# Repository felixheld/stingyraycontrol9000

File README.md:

# stingyraycontrol9000

This device combines the WS2801 led driver chip with the constant current LED driver modules from the Meanwell LDD series to get a relatively cheap digitally controllable cascadeable constant current LED driver for powerful LEDs that can be used in art installations.

If you have the PCB version 1.0, you'll need to bridge pins 3 and 4 of U1; this bug is fixed in version 1.1. We had some WS2801 chips that didn't change their behavior when connecting the polarity select pin to ground, so beware when you use WS2801 chips bought from different vendors; we didn't test if the visually different chips from a different vendor showed the same behaviour.

Do not hot-plug the modules without verifying that the ground connection is made first; otherwise you might end up with fried WS2801 chips.

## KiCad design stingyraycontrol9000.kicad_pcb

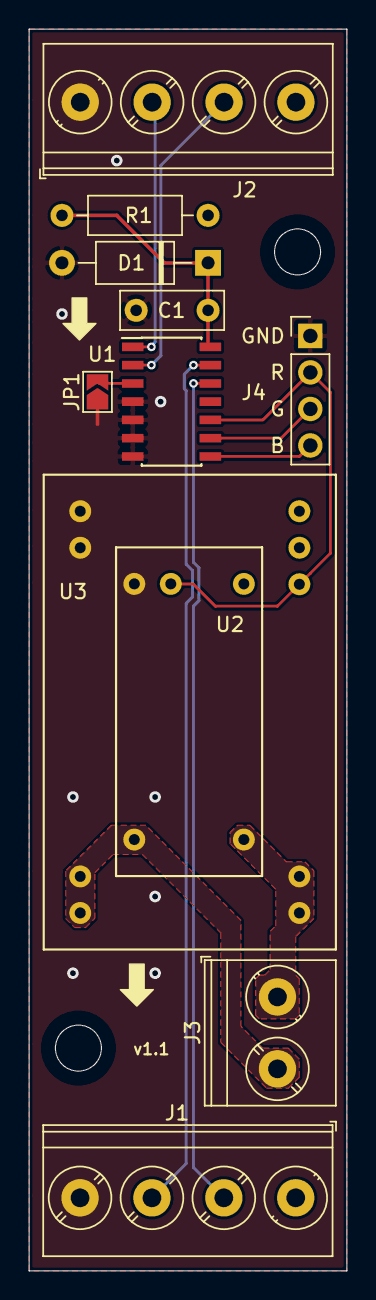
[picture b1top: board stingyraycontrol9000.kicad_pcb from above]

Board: 2 copper layers, 22.1 x 86.4 mm, 13 parts (0 on the bottom side), 13 nets.

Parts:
C1: 1u; C_Rect_L7.0mm_W2.5mm_P5.00mm
D1: D_Zener 5.1V; D_A-405_P10.16mm_Horizontal
J1, J2: Screw_Terminal_01x04; TerminalBlock_Phoenix_PT-1,5-4-5.0-H_1x04_P5.00mm_Horizontal
J3: Screw_Terminal_01x02; TerminalBlock_Phoenix_PT-1,5-2-5.0-H_1x02_P5.00mm_Horizontal
J4: Conn_01x04; PinHeader_1x04_P2.54mm_Vertical
JP1: SolderJumper_2_Open; SolderJumper-2_P1.3mm_Open_TrianglePad1.0x1.5mm
MK1, MK2: Mounting_Hole; MountingHole_3.2mm_M3_ISO14580
R1: R; R_Axial_DIN0207_L6.3mm_D2.5mm_P10.16mm_Horizontal
U1: ws2801; SOIC-14_3.9x8.7mm_P1.27mm
U2: LDD-L; LDD_L
U3: LDD-H; LDD_H

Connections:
+5V: C1.1, D1.1, R1.2, U1.14
+24V: J1.1, J2.4, R1.1, U2.1, U3.23, U3.24
/BOUT: J4.4, U1.8
/CKI: J2.2, U1.1
/CKO: J1.3, U1.13
/GOUT: J4.3, U1.9
/LED+: J3.1, U2.6, U3.13, U3.14
/LED-: J3.2, U2.5, U3.11, U3.12
/ROUT: J4.2, U1.10, U2.3, U3.22
/SDI: J2.3, U1.2
/SDO: J1.2, U1.12
/polarity: JP1.2, U1.3
GND: C1.2, D1.2, J1.4, J2.1, J4.1, JP1.1, U1.4, U1.5, U1.6, U1.7, U2.4, U3.1, U3.2

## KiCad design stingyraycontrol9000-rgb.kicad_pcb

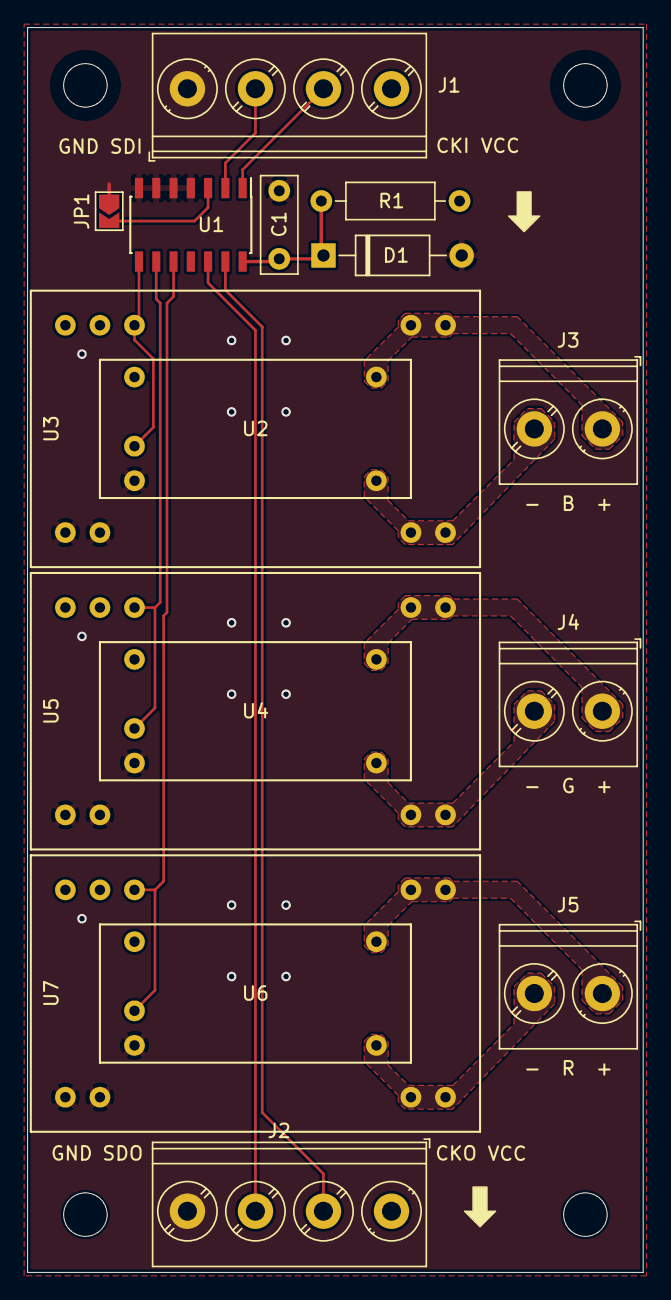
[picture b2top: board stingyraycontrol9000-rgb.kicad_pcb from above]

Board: 2 copper layers, 45.2 x 91.5 mm, 20 parts (0 on the bottom side), 17 nets.

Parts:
C1: 1u; C_Rect_L7.0mm_W2.5mm_P5.00mm
D1: D_Zener 5.1V; D_A-405_P10.16mm_Horizontal
J1, J2: Screw_Terminal_01x04; TerminalBlock_Phoenix_PT-1,5-4-5.0-H_1x04_P5.00mm_Horizontal
J3, J4, J5: Screw_Terminal_01x02; TerminalBlock_Phoenix_PT-1,5-2-5.0-H_1x02_P5.00mm_Horizontal
JP1: SolderJumper_2_Open; SolderJumper-2_P1.3mm_Open_TrianglePad1.0x1.5mm
MK1, MK2, MK3, MK4: Mounting_Hole; MountingHole_3.2mm_M3_ISO14580
R1: R; R_Axial_DIN0207_L6.3mm_D2.5mm_P10.16mm_Horizontal
U1: ws2801; SOIC-14_3.9x8.7mm_P1.27mm
U2, U4, U6: LDD-L; LDD_L
U3, U5, U7: LDD-H; LDD_H

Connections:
+5V: C1.1, D1.1, R1.2, U1.14
+24V: J1.4, J2.1, R1.1, U2.1, U3.23, U3.24, U4.1, U5.23, U5.24, U6.1, U7.23, U7.24
/B: U1.8, U2.3, U3.22
/B+: J3.1, U2.6, U3.13, U3.14
/B-: J3.2, U2.5, U3.11, U3.12
/CKI: J1.3, U1.1
/CKO: J2.2, U1.13
/G: U1.9, U4.3, U5.22
/G+: J4.1, U4.6, U5.13, U5.14
/G-: J4.2, U4.5, U5.11, U5.12
/R: U1.10, U6.3, U7.22
/R+: J5.1, U6.6, U7.13, U7.14
/R-: J5.2, U6.5, U7.11, U7.12
/SDI: J1.2, U1.2
/SDO: J2.3, U1.12
/polarity: JP1.2, U1.3
GND: C1.2, D1.2, J1.1, J2.4, JP1.1, U1.4, U1.5, U1.6, U1.7, U2.4, U3.1, U3.2, U4.4, U5.1, U5.2, U6.4, U7.1, U7.2

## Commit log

2019-01-05 add symbols and schematic
2019-01-05 add footprints for meanwell constant current led drivers
2019-01-05 add roughly placed, but not routed, pcb
2019-01-07 remove third mounting hole
2019-01-08 route board
2019-01-08 slight optimizations
2019-01-08 add library with logos
2019-01-08 add logos to pcb
2019-01-08 add README
2019-01-08 add cc by-sa 4.0 license
2019-01-08 set gerber output directory
2019-01-08 clean up zones and routing
2019-01-09 add gerber file release
2019-01-09 connect WS2801 polarity pin to ground and bump version to 1.1
2019-01-14 add values for R1
2019-01-15 add resistor value for 36V power supply
2019-02-03 add warning in readme file to not hot-plug the modules
2019-02-06 add pdf file of schematics
2019-02-06 add comment about WS2801 chips ignoring the state of the polarity selection pin
2019-02-06 fix typo and reword sentence
2019-03-21 add stingyray9000-rgb schematics
2019-03-21 stingyraycontrol9000-rgb: add layout
2019-03-21 stingyraycontrol9000: add solder jumper for polarity selection
